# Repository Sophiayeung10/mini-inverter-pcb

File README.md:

# Mini Inverter PCB Design

A compact printed circuit board (PCB) design created in KiCad. This repository contains the complete design package, including schematics, PCB layout, 3D component CAD models, Bill of Materials (BOM), and production-ready Gerber manufacturing files.

---

##  Project Overview

- **Toolchain**: KiCad (Schematic Editor, PCB Editor, 3D Viewer)
- **Layer Count**: 2-Layer PCB (Front Copper `F.Cu`, Bottom Copper `B.Cu`)
- **Key Features**: Integrated ground copper fills, manual 3D STEP component mapping, defined track width/via rules, and exported manufacturing deliverables.

---

##  Step-by-Step Design Workflow

### 1. Schematic Capture & Setup
- **Page & Grid Setup**: Configured project title and grid dimensions. Set up auto-save intervals to preserve progress.
- **Component Placement & Connections**: Placed schematic symbols, power flags, and ground references (`P1 to P5`). Wired components using orthogonal line modes and global labels for net organization.
- **Annotation & Footprint Assignment**: Automatically annotated schematic symbols and mapped components to footprints using preview and 3D verification tools.
- **Bill of Materials (BOM)**: Exported structured BOM data (`.csv`) directly from schematic attributes.

---

### 2. PCB Layout & Board Design
- **Board Outline & Mechanicals**: Defined physical dimensions using the `Edge.Cuts` layer and configured mounting hole placements.
- **3D Model Integration**: Linked custom 3D STEP models (e.g., terminal blocks from GrabCAD) with precise alignment and rotation offsets for 3D Viewer verification.
- **Design Rule Definition**: Established custom trace widths and via parameters for power and signal routing.

---

### 3. Routing & Power Planes
- **Signal & Power Routing**: Routed top (`F.Cu`) and bottom (`B.Cu`) copper layers using single-track routing and layer-switching via placements (`V`).
- **Ground Fills (Pour Zones)**: Created top and bottom ground planes (`GND` net) using copper zones (`B` key rebuild) to optimize return paths instead of drawing thin wires for every return pathand thermal management. Current flows back easily, and the board stays cooler.

---

### 4. Manufacturing & Export Deliverables
- **Gerber & Drill Generation**: Plotted fabrication files (Gerbers) and drill maps into a structured release directory.
- **Archive Package**: Generated a consolidated `.zip` production package containing all Gerber and drill data, ready for PCB manufacturing submission.

---

## 5. Challenges in My Mini Inverter PCB Project

### 1. Net Name Mismatch

While wiring the board, I noticed that one of the ports I wanted to connect turned grey and wouldn't accept a connection. At first I thought KiCad was broken, but the real cause was simple: the two ends didn't share the same net name.

KiCad doesn't connect things by how they look on screen. It connects them by **name**. If one side is called `VIN` and the other is `Vin` or `VIN1`, KiCad treats them as two unrelated connections, and the mismatched port is greyed out.

**Solution:** I standardized the label names, ran the Electrical Rules Check (ERC), and updated the PCB from the schematic (`F8`).

### 2. Aligning Custom 3D Models

Downloaded STEP files (such as the GrabCAD terminal blocks) rarely line up on import. Fixing the position, rotation, and scale by hand takes trial and error to match my PCB design.

**Solution:** I adjusted the offset and rotation values in the footprint's 3D model settings and checked the result in the 3D Viewer until it matched the PCB.

---

##  Project Visuals

| 2D PCB Layout | 3D Board Render |
| :---: | :---: |
|  |  |

---

##  Repository Structure

```text
├── Mini Inverter/          # Project sub-folder / CAD assets
├── images/                 # Screenshots (2D layout, 3D render)
├── .gitignore              # Files Git should ignore
├── README.md               # Project documentation
├── kicad 1.kicad_pro       # Main KiCad project file
├── kicad 1.kicad_sch       # Schematic source file
├── kicad 1.kicad_pcb       # PCB layout file
├── kicad 1.csv             # Bill of Materials (BOM)
└── kicad 1.zip             # Manufacturing package (Gerbers & drill files)

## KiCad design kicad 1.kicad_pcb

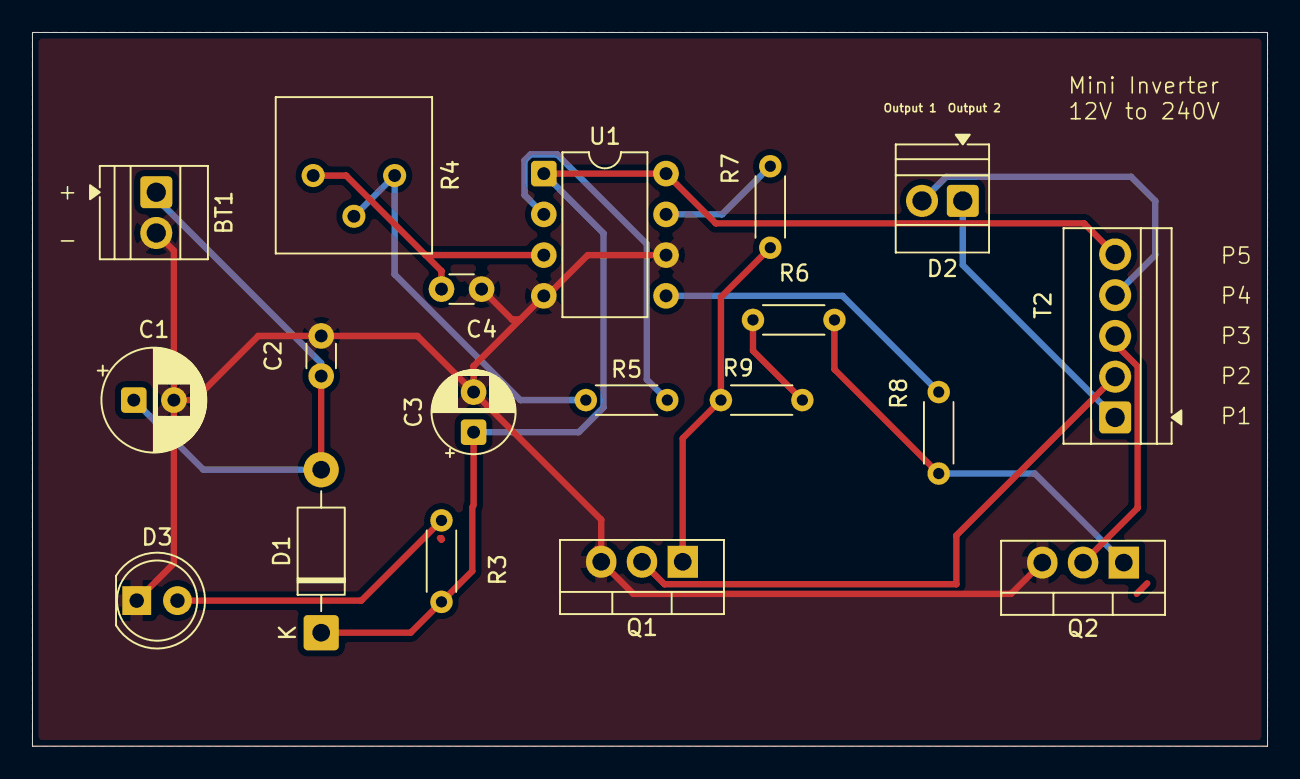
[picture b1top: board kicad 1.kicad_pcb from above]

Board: 2 copper layers, 77.0 x 44.5 mm, 19 parts (0 on the bottom side), 14 nets.

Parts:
BT1: 12V; TerminalBlock_Xinya_XY308-2.54-2P_1x02_P2.54mm_Horizontal
C1: 470uF; CP_Radial_D6.3mm_P2.50mm
C2: 0.01uF; C_Disc_D3.0mm_W1.6mm_P2.50mm
C3: 47uF; CP_Radial_D5.0mm_P2.50mm
C4: 0.2uF; C_Disc_D3.0mm_W1.6mm_P2.50mm
D1: D; D_DO-41_SOD81_P10.16mm_Horizontal
D2: LED; TerminalBlock_Xinya_XY308-2.54-2P_1x02_P2.54mm_Horizontal
D3: LED; LED_D5.0mm
Q1, Q2: IRLZ24; TO-220-3_Vertical
R3: R; R_Axial_DIN0204_L3.6mm_D1.6mm_P5.08mm_Horizontal
R4: 22K; Potentiometer_Bourns_3386P_Vertical
R5: 22K; R_Axial_DIN0204_L3.6mm_D1.6mm_P5.08mm_Horizontal
R6, R9: 1K; R_Axial_DIN0204_L3.6mm_D1.6mm_P5.08mm_Horizontal
R7, R8: 22R; R_Axial_DIN0204_L3.6mm_D1.6mm_P5.08mm_Horizontal
T2: Transformer_SP_1S; TerminalBlock_Xinya_XY308-2.54-5P_1x05_P2.54mm_Horizontal
U1: IR2153; DIP-8_W7.62mm

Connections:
GND: BT1.2 (-), C1.2, C2.2, C3.2, C4.1, D3.1 (K), Q1.3 (S), Q2.3 (S), U1.4 (COM), U1.6 (VS)
Input: C3.1, D1.1 (K), R3.2, T2.5 (S2), U1.1 (VCC), U1.8 (VB)
unnamed: BT1.1 (+), C1.1, C2.1, D1.2 (A)
unnamed: D3.2 (A), R3.1
unnamed: D2.2 (A), T2.4 (S1)
unnamed: Q1.1 (G), R7.1, R9.1
unnamed: R6.1, R8.2, R9.2, U1.5 (LO)
unnamed: D2.1 (K), R4.2, R4.3, R5.1, T2.1 (PR1)
unnamed: C4.2, R4.1, U1.3 (CT)
unnamed: R7.2, U1.7 (HO)
unnamed: Q2.1 (G), R6.2, R8.1
unnamed: R5.2, U1.2 (RT)
Output 1: Q1.2 (D), T2.2 (PM)
Output 3: Q2.2 (D), T2.3 (PR2)
